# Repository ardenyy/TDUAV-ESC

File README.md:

# TDUAV-ESC
Electronic Speed Controller for BLDC Motors with 3A UBEC.

Made for UAV Team "**TDUAV**" at Turkish-German University.
- Atmega328P-AU Microcontroller
- Designed for 3S Li-Po Batteries
- BEMF Detection
- 5V/3A UBEC Circuit
- Up to 50A current sensing
- 35A Continuous, 50A Burst current output
- 100mm x 70mm

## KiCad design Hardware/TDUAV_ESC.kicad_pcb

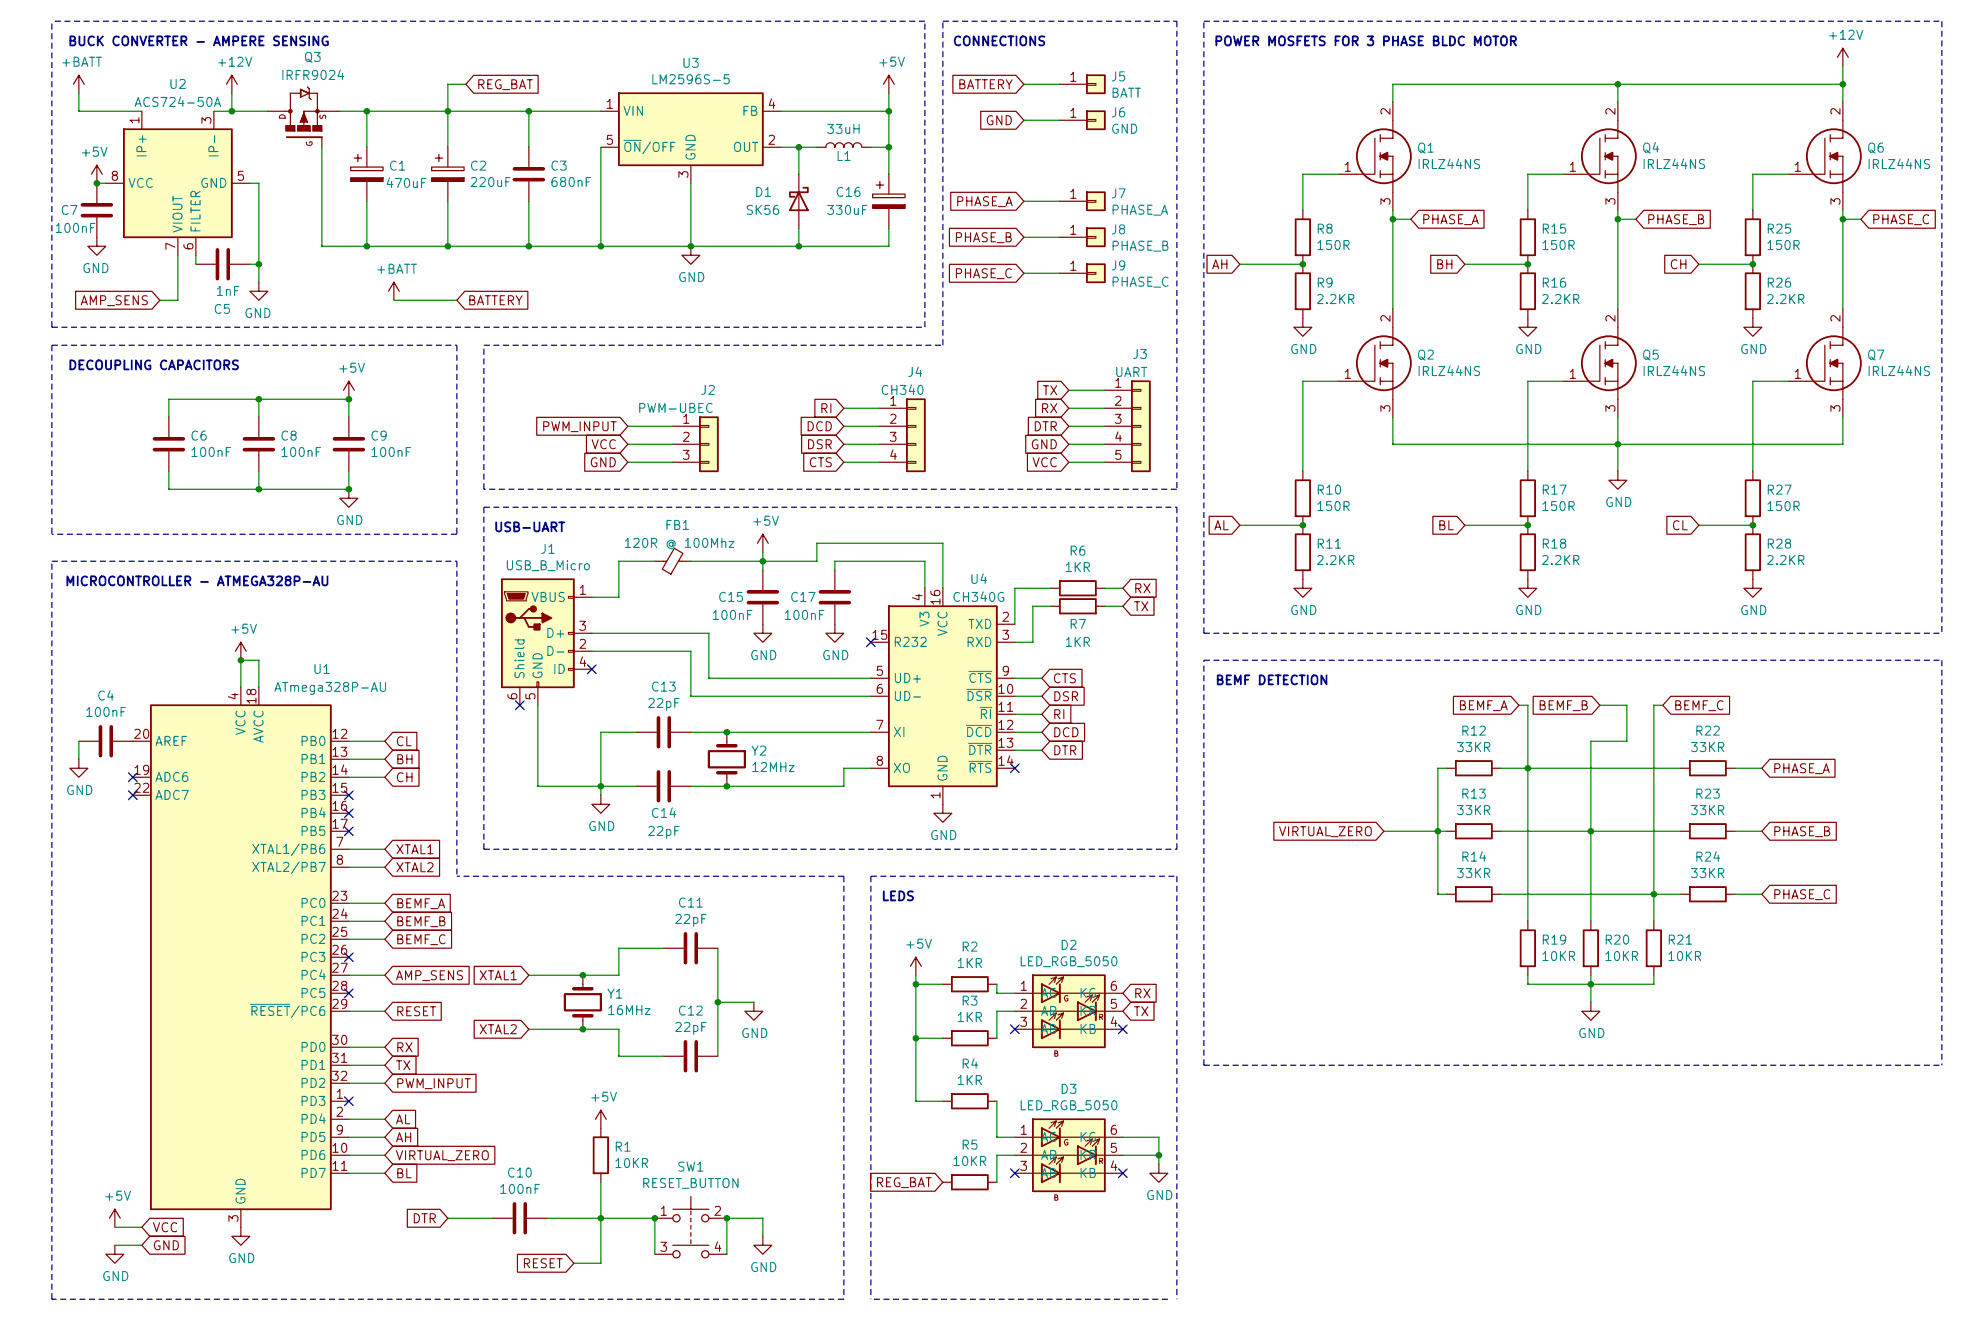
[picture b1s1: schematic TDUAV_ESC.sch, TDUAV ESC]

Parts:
C1: 470uF; CP_Elec_10x10
C2: 220uF; CP_Elec_10x10
C3: 680nF; C_1206_3216Metric_Pad1.33x1.80mm_HandSolder
C4, C6, C7, C8, C9, C10, C15, C17: 100nF; C_1206_3216Metric_Pad1.33x1.80mm_HandSolder
C5: 1nF; C_1206_3216Metric_Pad1.33x1.80mm_HandSolder
C11, C12, C13, C14: 22pF; C_1206_3216Metric_Pad1.33x1.80mm_HandSolder
C16: 330uF; CP_Elec_10x10
D1: SK56; D_SMC_Handsoldering
D2, D3: LED_RGB_5050; LED_RGB_5050-6
FB1: 120R @ 100Mhz; L_1206_3216Metric_Pad1.22x1.90mm_HandSolder
J1: USB_B_Micro; USB_Micro-B_Molex_47346-0001
J2: PWM-UBEC; PinHeader_1x03_P2.54mm_Vertical
J3: UART; PinHeader_1x05_P2.54mm_Vertical
J4: CH340; PinHeader_1x04_P2.54mm_Vertical
J5: BATT; SolderWirePad_1x01_SMD_5x10mm
J6: GND; SolderWirePad_1x01_SMD_5x10mm
J7: PHASE_A; SolderWirePad_1x01_SMD_5x10mm
J8: PHASE_B; SolderWirePad_1x01_SMD_5x10mm
J9: PHASE_C; SolderWirePad_1x01_SMD_5x10mm
L1: 33uH; INDUCTOR_SMD_12X12X8
Q1, Q2, Q4, Q5, Q6, Q7: IRLZ44NS; IRF2804STRLPBF; Manufacturer_Part_Number IRLZ44NSTRLPBF; Mouser Part Number 942-IRLZ44NSTRLPBF
Q3: IRFR9024; DPAK
R1, R5, R19, R20, R21: 10KR; R_2512_6332Metric_Pad1.40x3.35mm_HandSolder
R2, R3, R4, R6, R7: 1KR; R_2512_6332Metric_Pad1.40x3.35mm_HandSolder
R8, R10, R15, R17, R25, R27: 150R; R_2512_6332Metric_Pad1.40x3.35mm_HandSolder
R9, R11, R16, R18, R26, R28: 2.2KR; R_2512_6332Metric_Pad1.40x3.35mm_HandSolder
R12, R13, R14, R22, R23, R24: 33KR; R_2512_6332Metric_Pad1.40x3.35mm_HandSolder
SW1: RESET_BUTTON; SW_PUSH_4_6X6mm_H3.1mm
U1: ATmega328P-AU; TQFP-32_7x7mm_P0.8mm
U2: ACS724-50A; SOIC-8_3.9x4.9mm_P1.27mm
U3: LM2596S-5; TO-263-5_TabPin3
U4: CH340G; SOIC-16_3.9x9.9mm_P1.27mm
Y1: 16MHz; Crystal_SMD_HC49-SD
Y2: 12MHz; Crystal_SMD_HC49-SD

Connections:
+12V: Q1.2, Q3.4, Q4.2, Q6.2, U2.3 (IP-), U2.4 (IP-)
AH: R8.2, R9.1, U1.9 (PD5)
AL: R10.2, R11.1, U1.2 (PD4)
AMP_SENS: U1.27 (PC4), U2.7 (VIOUT)
BATTERY: J5.1, U2.1 (IP+), U2.2 (IP+)
BEMF_A: R12.1, R19.1, R22.2, U1.23 (PC0)
BEMF_B: R13.1, R20.1, R23.2, U1.24 (PC1)
BEMF_C: R14.1, R21.1, R24.2, U1.25 (PC2)
BH: R15.2, R16.1, U1.13 (PB1)
BL: R17.2, R18.1, U1.11 (PD7)
CH: R25.2, R26.1, U1.14 (PB2)
CL: R27.2, R28.1, U1.12 (PB0)
CTS: J4.4, U4.9 (~CTS)
DCD: J4.2, U4.12 (~DCD)
DSR: J4.3, U4.10 (~DSR)
DTR: C10.2, J3.3, U4.13 (~DTR)
GND: C1.2, C2.2, C3.2, C4.2, C5.2, C6.2, C7.2, C8.2, C9.2, C11.1, C12.1, C13.2, C14.2, C15.1, C16.2, C17.1, D1.2 (A), D3.5 (KR), D3.6 (KG), J1.5 (GND), J2.3, J3.4, J6.1, Q2.3, Q3.1, Q5.3, Q7.3, R9.2, R11.2, R16.2, R18.2, R19.2, R20.2, R21.2, R26.2, R28.2, SW1.2, SW1.4, U1.3 (GND), U1.5 (GND), U1.21 (GND), U2.5 (GND), U3.3 (GND), U3.5 (~ON~/OFF), U4.1 (GND)
unnamed: C4.1, U1.20 (AREF)
unnamed: C5.1, U2.6 (FILTER)
unnamed: C13.1, U4.7 (XI), Y2.1
unnamed: C14.1, U4.8 (XO), Y2.2
unnamed: C17.2, U4.4 (V3)
unnamed: D1.1 (K), L1.1, U3.2 (OUT)
unnamed: D2.1 (AG), R2.1
unnamed: D2.2 (AR), R3.1
unnamed: D3.1 (AG), R4.1
unnamed: D3.2 (AR), R5.1
unnamed: FB1.1, J1.1 (VBUS)
unnamed: J1.2 (D-), U4.6 (UD-)
unnamed: J1.3 (D+), U4.5 (UD+)
unnamed: Q1.1, R8.1
unnamed: Q2.1, R10.1
unnamed: Q4.1, R15.1
unnamed: Q5.1, R17.1
unnamed: Q6.1, R25.1
unnamed: Q7.1, R27.1
unnamed: R6.2, U4.2 (TXD)
unnamed: R7.1, U4.3 (RXD)
PHASE_A: J7.1, Q1.3, Q2.2, R22.1
PHASE_B: J8.1, Q4.3, Q5.2, R23.1
PHASE_C: J9.1, Q6.3, Q7.2, R24.1
PWM_INPUT: J2.1, U1.32 (PD2)
REG_BAT: C1.1, C2.1, C3.1, Q3.3, R5.2, U3.1 (VIN)
RESET: C10.1, R1.2, SW1.1, SW1.3, U1.29 (~RESET~/PC6)
RI: J4.1, U4.11 (~RI)
RX: D2.6 (KG), J3.2, R6.1, U1.30 (PD0)
TX: D2.5 (KR), J3.1, R7.2, U1.31 (PD1)
VCC: C6.1, C7.1, C8.1, C9.1, C15.2, C16.1, FB1.2, J2.2, J3.5, L1.2, R1.1, R2.2, R3.2, R4.2, U1.4 (VCC), U1.6 (VCC), U1.18 (AVCC), U2.8 (VCC), U3.4 (FB), U4.16 (VCC)
VIRTUAL_ZERO: R12.2, R13.2, R14.2, U1.10 (PD6)
XTAL1: C11.2, U1.7 (XTAL1/PB6), Y1.1
XTAL2: C12.2, U1.8 (XTAL2/PB7), Y1.2

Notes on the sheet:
BUCK CONVERTER - AMPERE SENSING
DECOUPLING CAPACITORS
LEDS
USB-UART
BEMF DETECTION
MICROCONTROLLER - ATMEGA328P-AU
POWER MOSFETS FOR 3 PHASE BLDC MOTOR
CONNECTIONS

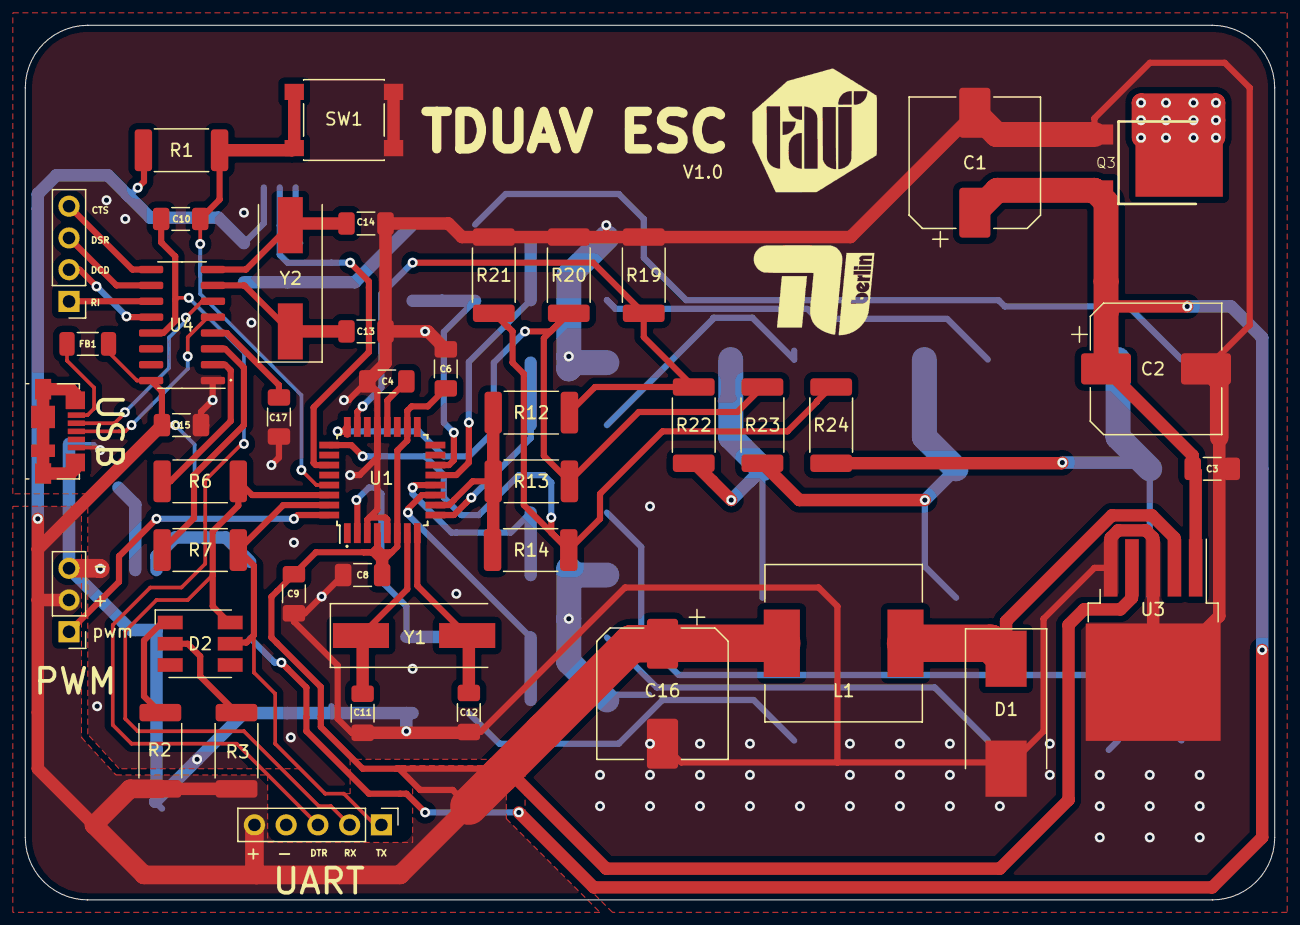
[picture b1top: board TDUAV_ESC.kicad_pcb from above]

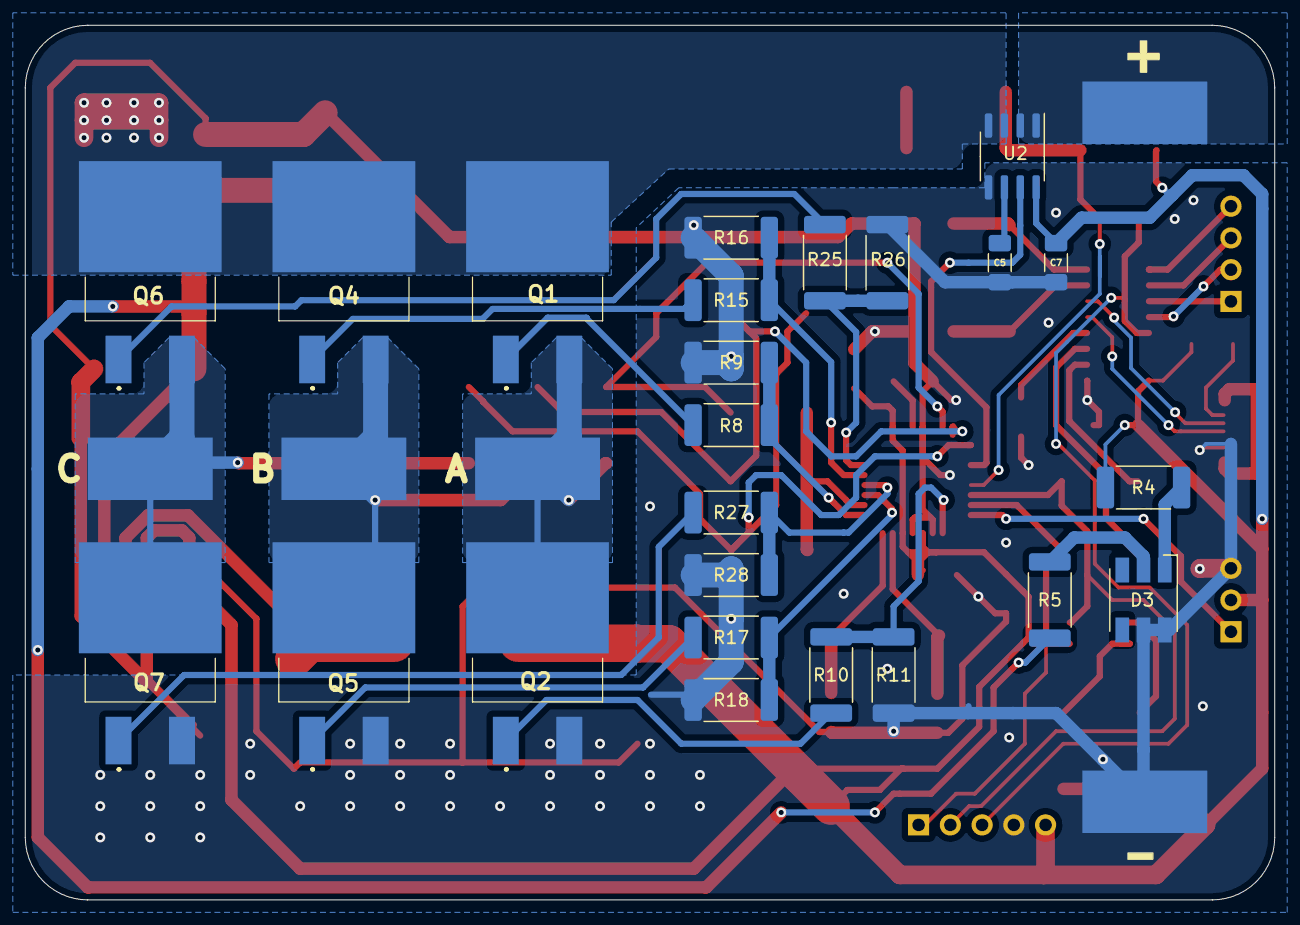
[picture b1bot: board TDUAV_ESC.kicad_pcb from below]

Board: 2 copper layers, 100.0 x 70.0 mm, 73 parts (29 on the bottom side), 51 nets.

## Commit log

2021-06-24 Added PCB images for preview
2021-06-29 Edited Silkscreens
2021-06-29 Edited README
2021-07-01 Updated PCB 3D Images
2021-07-16 Added cap to ch340 and changed values of decoupling caps
2021-07-19 Updated PCB design
